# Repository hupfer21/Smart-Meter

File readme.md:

# Smart Meter

This project is a three-phase smart meter based on the ATM90E36 energy metering IC.

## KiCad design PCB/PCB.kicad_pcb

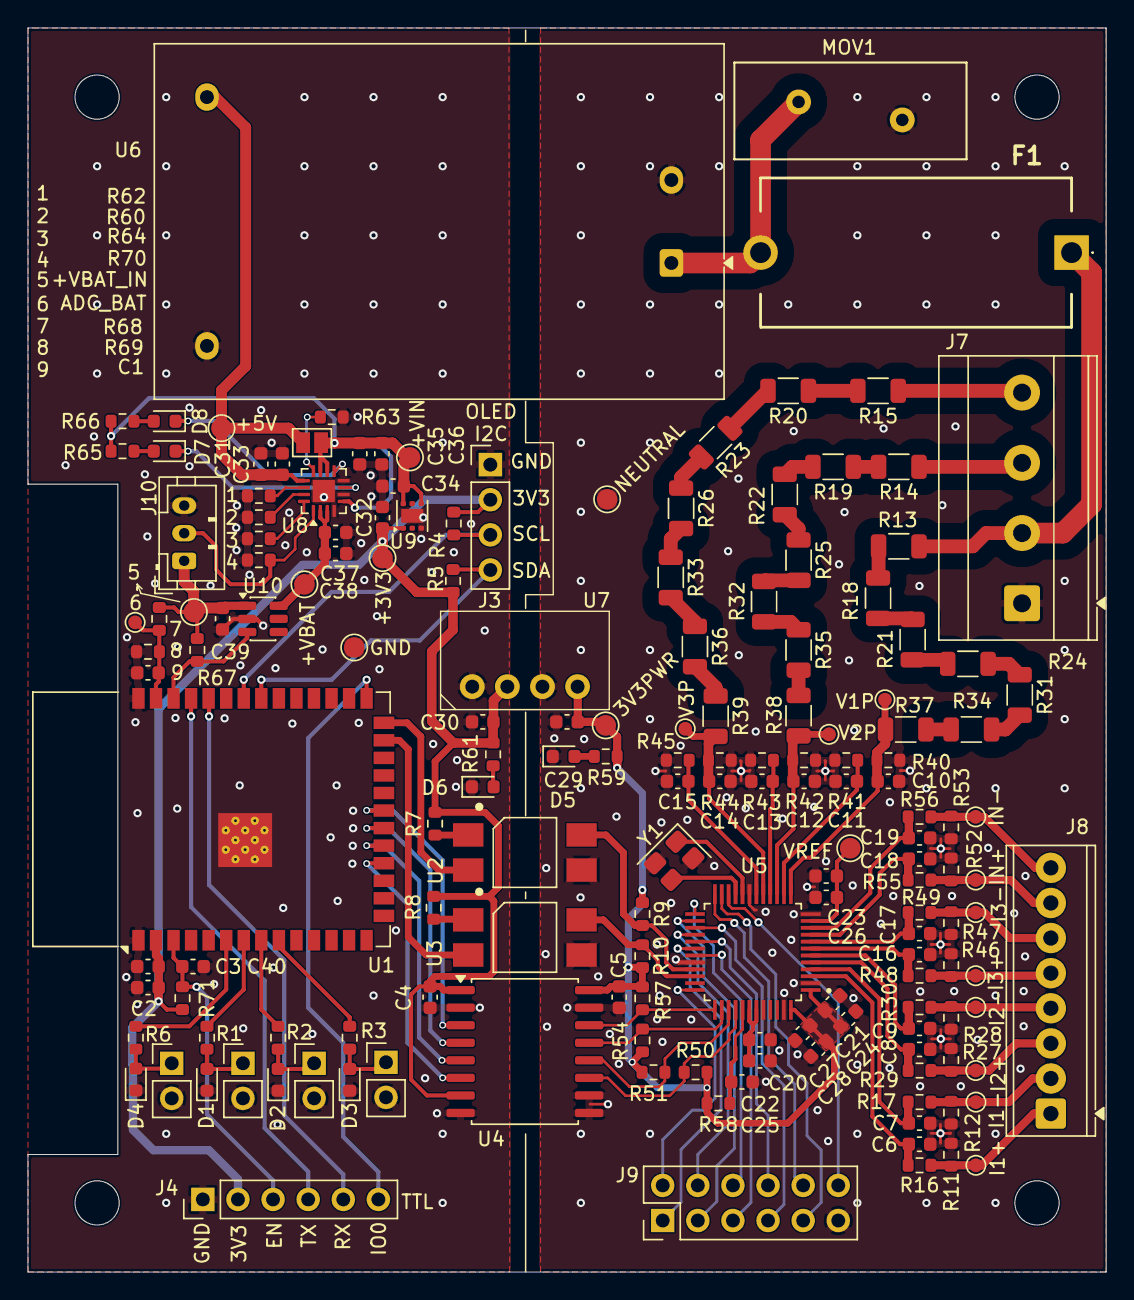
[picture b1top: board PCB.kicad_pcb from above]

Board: 2 copper layers, 78.0 x 90.0 mm, 168 parts (0 on the bottom side), 109 nets.

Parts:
C1, C3, C4, C5, C20, C21, C22, C24, C27, C28, C33, C37, C40: 100n/16V; C_0603_1608Metric
C2, C23, C25, C26, C29, C30, C35, C36, C39: 10u/16V; C_0603_1608Metric
C6, C7, C8, C9, C10, C11, C12, C13, C14, C15, C16, C17, C18, C19: 18n/10Q; C_0603_1608Metric
C31, C32, C34, C38: 1u/16V; C_0603_1608Metric
D1: LED_L1; LED_0603_1608Metric
D2: LED_L2; LED_0603_1608Metric
D3, D4: LED_L3; LED_0603_1608Metric
D5, D6, D7, D8: LED; LED_0603_1608Metric
F1: T/200mA/250VAC; FuseHolder_5x20mm_P=22,5mm
H1, H2, H3, H4: MountingHole; MountingHole_3.2mm_M3
J1, J2, J5, J6: Conn_01x02; PinHeader_1x02_P2.54mm_Vertical
J3: Conn_01x04; PinHeader_1x04_P2.54mm_Vertical
J4: Conn_01x06; PinHeader_1x06_P2.54mm_Vertical
J7: Screw_Terminal_01x04; TerminalBlock_Phoenix_MKDS-3-4-5.08_1x04_P5.08mm_Horizontal
J8: Screw_Terminal_01x08; TerminalBlock_Phoenix_MPT-0,5-8-2.54_1x08_P2.54mm_Horizontal
J9: Conn_02x06_Odd_Even; PinHeader_2x06_P2.54mm_Vertical
J10: Conn_01x03; JST_PH_B3B-PH-K_1x03_P2.00mm_Vertical
JP1: SolderJumper_2_Open; SolderJumper-2_P1.3mm_Open_Pad1.0x1.5mm
MOV1: 14D471K; RV_Disc_D16.5mm_W6.7mm_P7.5mm
R1, R2, R3, R6, R7, R8, R59, R61, R65, R66: 1k; R_0603_1608Metric
R4, R5, R9, R10, R50, R51, R54, R57, R58, R67, R68, R69, R70, R71: 10k; R_0603_1608Metric
R11, R12, R27, R28, R46, R47, R52, R53: 2R4/1Q; R_0603_1608Metric
R13, R14, R15, R18, R19, R20, R21, R22, R23, R24, R25, R26, R31, R32, R33, R34, R35, R36, R37, R38, R39: 240k/1Q; R_1206_3216Metric
R16, R17, R29, R30, R40, R41, R42, R43, R44, R45, R48, R49, R55, R56: 1k/1Q; R_0603_1608Metric
R60: 91R/1Q; R_0603_1608Metric
R62: 56k/1Q; R_0603_1608Metric
R63: 1k58/1Q; R_0603_1608Metric
R64: 1k8/1Q; R_0603_1608Metric
TP1, TP13, TP14, TP15, TP16, TP17, TP18, TP19, TP21: TestPoint; TestPoint_Pad_D1.5mm
TP2, TP3, TP4, TP5, TP6, TP7, TP8, TP9, TP10, TP11, TP12, TP20: TestPoint; TestPoint_Pad_D1.0mm
U1: ESP32-S3; ESP32-S3-WROOM-1
U2, U3: PC817; SOIC-4_6.5x4.6_P2.54mm
U4: ADuM1411; SOIC-16W_7.5x10.3mm_P1.27mm
U5: ATM90E36A-AU-R; 48TQFP
U6: HLK-5M05; Converter_ACDC_Hi-Link_HLK-5Mxx
U7: B0303S-1WR3
U8: BQ24073RGT; VQFN-16-1EP_3x3mm_P0.5mm_EP1.6x1.6mm
U9: TLV75733PDRV; WSON-6-1EP_2x2mm_P0.65mm_EP1x1.6mm
U10: TPS22918DBV; SOT-23-6
Y1: ABM8W-16.3840MHZ-4-B1U-T3; Crystal_SMD_3225-4Pin_3.2x2.5mm

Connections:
+3V3: C2.1, C3.1, C4.1, C30.1, C32.1, J3.2, J4.2, R4.1, R5.1, R7.1, R8.1, R61.1, R71.1, TP16.1 (1_1), U1.2 (3V3), U4.1 (VDD1), U4.7 (CTRL1), U7.2 (+Vin), U9.1 (OUT)
+3V3PWR: C5.1, C21.1, C24.1, C27.1, C28.1, C29.1, R9.1, R10.1, R50.1, R51.1, R54.1, R57.1, R58.1, R59.1, TP14.1 (1_1), U4.16 (VDD2), U5.1 (AVDD), U5.48 (DVDD), U7.4 (+Vout)
+5V_EXT: C31.1, C33.1, JP1.1 (A), TP15.1 (1_1), U6.4 (+Vout), U8.13 (IN)
+VBAT: C37.1, C38.1, TP18.1 (1_1), U8.2 (BAT), U8.3 (BAT), U10.6 (VOUT)
+VBAT_IN: C39.1, J10.1, R67.1, R68.1, TP19.1 (1_1), U10.1 (VIN)
+VIN: C34.1, C35.1, C36.1, JP1.2 (B), R65.1, R66.1, TP17.1 (1_1), U8.5 (EN2), U8.10 (OUT), U8.11 (OUT), U9.4 (EN), U9.6 (IN)
/CF1: J9.6, U5.25 (CF1)
/CF2: J9.3, U5.26 (CF2)
/CF3: J9.7, U5.27 (CF3)
/CF4: J9.4, U5.28 (CF4)
/CHG: D8.1 (K), U8.9 (~CHG)
/DMA: J9.2, U5.36 (DMA_CTRL)
/EN: C40.1, J4.3, R71.2, U1.3 (EN)
/I1N: C7.2, R17.2, U5.4 (I1N)
/I1P: C6.1, R16.2, U5.3 (I1P)
/I2N: C9.2, R30.2, U5.6 (I2N)
/I2P: C8.1, R29.2, U5.5 (I2P)
/I3N: C17.2, R49.2, U5.8 (I3N)
/I3P: C16.1, R48.2, U5.7 (I3P)
/I4N: C19.2, R56.2, U5.10 (I4N)
/I4P: C18.1, R55.2, U5.9 (I4P)
/ILIM: R63.1, U8.12 (ILIM)
/IO0: J4.6, U1.27 (IO0)
/IRQ0: J9.1, U5.30 (IRQ0)
/IRQ1: J9.5, U5.31 (IRQ1)
/ISET: R64.1, U8.16 (ISET)
/LED_L1: R1.1, U1.7 (IO7)
/LED_L2: R2.1, U1.8 (IO15)
/LED_L3: R3.1, U1.9 (IO16)
/LED_WIFI: R6.1, U1.6 (IO6)
/MCU_CS: U1.21 (IO13), U4.3 (VIA)
/MCU_MISO: U1.18 (IO10), U4.6 (VOD)
/MCU_MOSI: U1.19 (IO11), U4.5 (VIC)
/MCU_SCLK: U1.20 (IO12), U4.4 (VIB)
/OSCI: U5.20 (OSCI), Y1.1
/OSCO: U5.21 (OSCO), Y1.3
/PG: D7.1 (K), U8.7 (~PGOOD)
/PMC_0: U1.26 (IO45), U2.2
/PMC_1: U1.25 (IO48), U3.2
/RXD0: J4.5, U1.36 (RXD0)
/SCL: J3.3, R4.2, U1.34 (IO41)
/SDA: J3.4, R5.2, U1.33 (IO40)
/TD: R60.1, U8.15 (TD)
/TMR: R62.1, U8.14 (TMR)
/TS: J10.2, R70.1, U8.1 (TS)
/TXD0: J4.4, U1.37 (TXD0)
/V1N: C11.2, R41.1, U5.14 (V1N)
/V1P: C10.1, R37.2, R40.2, TP8.1 (1_1), U5.13 (V1P)
/V2N: C13.2, R43.1, U5.16 (V2N)
/V2P: C12.1, R38.2, R42.2, TP9.1 (1_1), U5.15 (V2P)
/V3N: C15.2, R45.1, U5.18 (V3N)
/V3P: C14.1, R39.2, R44.2, TP10.1 (1_1), U5.17 (V3P)
/VREF: C23.1, C26.1, TP13.1 (1_1), U5.11 (VREF)
/WARN: J9.8, U5.29 (WARNOUT)
/ZX0: J9.12, U5.22 (ZX0)
/ZX1: J9.9, U5.23 (ZX1)
/ZX2: J9.10, U5.24 (ZX2)
ADC_BAT: C1.1, R68.2, R69.1, TP20.1 (1_1), U1.39 (IO1)
BAT_SW: R67.2, U1.38 (IO2), U10.3 (ON)
GND: C1.2, C2.2, C3.2, C4.2, C30.2, C31.2, C32.2, C33.2, C34.2, C35.2, C36.2, C37.2, C38.2, C39.2, C40.2, D1.1 (K), D2.1 (K), D3.1 (K), D4.1 (K), D6.1 (K), J1.2, J2.2, J3.1, J4.1, J5.2, J6.2, J10.3, R60.2, R62.2, R63.2, R64.2, R69.2, R70.2, TP21.1 (1_1), U1.1 (GND), U1.40 (GND), U1.41 (GND), U4.2 (GND1), U4.8 (GND1), U6.3 (-Vout), U7.1 (-Vin), U8.4 (~CE), U8.6 (EN1), U8.8 (VSS), U8.17 (VSS), U9.3 (GND), U9.7 (GND), U10.2 (GND)
I1+: J8.1, R11.2, R16.1, TP2.1 (1_1)
I1-: J8.2, R12.1, R17.1, TP3.1 (1_1)
I2+: J8.3, R27.2, R29.1, TP4.1 (1_1)
I2-: J8.4, R28.1, R30.1, TP5.1 (1_1)
I3+: J8.5, R46.2, R48.1, TP6.1 (1_1)
I3-: J8.6, R47.1, R49.1, TP7.1 (1_1)
IN+: J8.7, R52.2, R55.1, TP11.1 (1_1)
IN-: J8.8, R53.1, R56.1, TP12.1 (1_1)
L1: F1.1, J7.2, R13.1
L2: J7.3, R14.1
L3: J7.4, R15.1
MISO: R50.2, U4.11 (VID), U5.40 (SDI)
MOSI: R51.2, U4.12 (VOC), U5.39 (SD0)
N: C5.2, C6.2, C7.1, C8.2, C9.1, C10.2, C11.1, C12.2, C13.1, C14.2, C15.1, C16.2, C17.1, C18.2, C19.1, C20.2, C21.2, C22.2, C23.2, C24.2, C25.2, C26.2, C27.2, C28.2, C29.2, D5.1 (K), J7.1, J9.11, MOV1.2, R11.1, R12.2, R27.1, R28.2, R40.1, R41.2, R42.1, R43.2, R44.1, R45.2, R46.1, R47.2, R52.1, R53.2, TP1.1 (1_1), U2.3, U3.3, U4.9 (GND2), U4.10 (CTRL2), U4.15 (GND2), U5.2 (AGND), U5.12 (AGND), U5.19 (DGND), U5.32 (TEST), U5.44 (DGND), U5.47 (DGND), U6.2 (AC/N), U7.3 (-Vout), Y1.2 (G), Y1.4 (G)
unnamed: D1.2 (A), J1.1, R1.2
unnamed: D2.2 (A), J2.1, R2.2
unnamed: D3.2 (A), J5.1, R3.2
unnamed: D4.2 (A), J6.1, R6.2
unnamed: D5.2 (A), R59.2
unnamed: D6.2 (A), R61.2
unnamed: D7.2 (A), R65.2
unnamed: D8.2 (A), R66.2
unnamed: R7.2, U2.1
unnamed: R8.2, U3.1
unnamed: R13.2, R18.1
unnamed: R14.2, R19.1
unnamed: R15.2, R20.1
unnamed: R18.2, R21.1
unnamed: R19.2, R22.1
unnamed: R20.2, R23.1
unnamed: R21.2, R24.1
unnamed: R22.2, R25.1
unnamed: R23.2, R26.1
unnamed: R24.2, R31.1
unnamed: R25.2, R32.1
unnamed: R26.2, R33.1
unnamed: R31.2, R34.1
unnamed: R32.2, R35.1
unnamed: R33.2, R36.1
unnamed: R34.2, R37.1
unnamed: R35.2, R38.1
unnamed: R36.2, R39.1
unnamed: C20.1, R58.2, U5.41 (~RESET)
unnamed: F1.2, MOV1.1, U6.1 (AC/L)
PM0: R9.2, U2.4, U5.33 (PM0)
PM1: R10.2, U3.4, U5.34 (PM1)
SCLK: R54.2, U4.13 (VOB), U5.38 (SCLK)
VDD18: C22.1, C25.1, U5.42 (VDD18), U5.43 (VDD18)
~CS: R57.2, U4.14 (VOA), U5.37 (~CS)
